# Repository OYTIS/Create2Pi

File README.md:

# Pi HAT for iRobot Create

iRobot Create Open Interface is a 7-pin mini-DIN connector exposing unregulated battery power pin and 5V UART. The HAT contains a power regulator to convert the battery power to 5V, and a level shifter to interface Roomba UART with Raspberry's 3.3V UART. Also a USB-Serial interface is added for convenience.

## Quickstart
TODO (when software is done)

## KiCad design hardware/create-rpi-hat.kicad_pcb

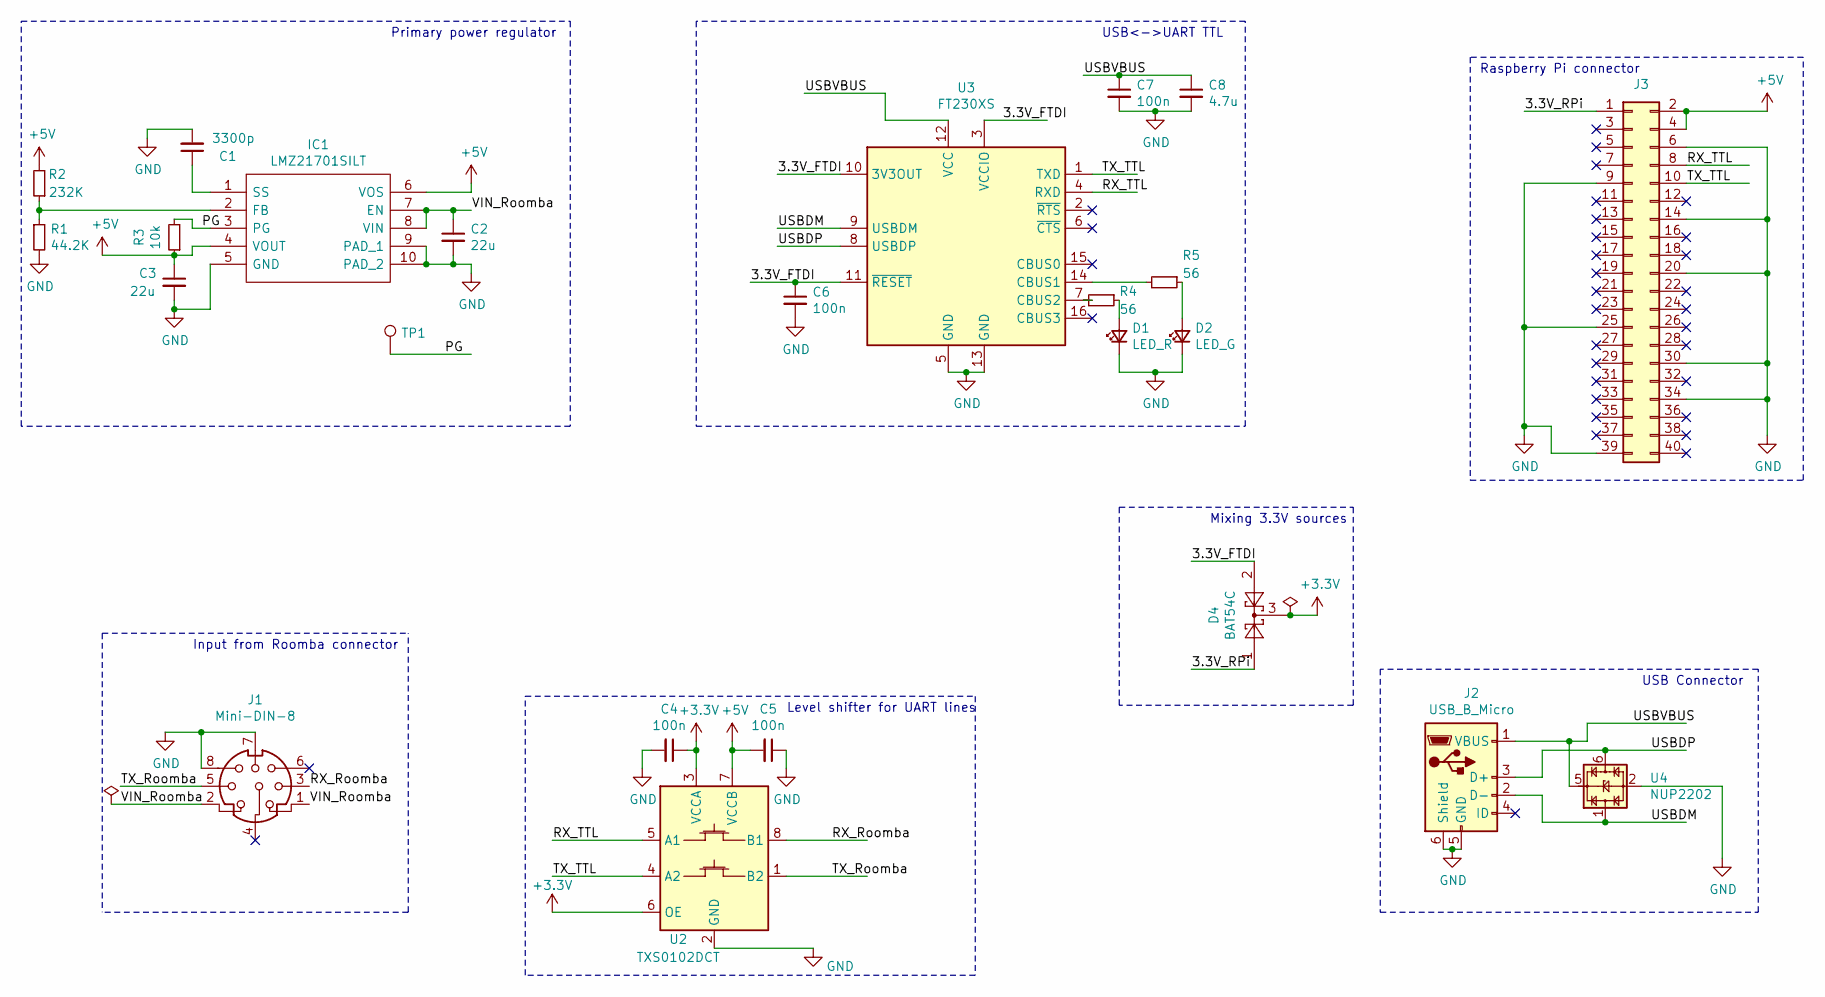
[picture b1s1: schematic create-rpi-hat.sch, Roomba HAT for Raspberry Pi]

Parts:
C1: 3300p; C_0402_1005Metric
C2, C3: 22u; C_0805_2012Metric_Pad1.15x1.40mm_HandSolder
C4, C5, C6, C7: 100n; C_0402_1005Metric
C8: 4.7u; C_0402_1005Metric
D1: LED_R; R_0402_1005Metric
D2: LED_G; R_0402_1005Metric
D4: BAT54C; SOT-23
IC1: LMZ21701SILT; SIL0008E; Mouser Part Number 595-LMZ21701SILT
J1: Mini-DIN-8; CUI_MD-80SM
J2: USB_B_Micro; USB_Micro-B_Molex-105017-0001
J3: RaspberryPi GPIO connector; PinSocket_2x20_P2.54mm_Vertical
R1: 44.2K; R_0402_1005Metric
R2: 232K; R_0402_1005Metric
R3: 10k; R_0402_1005Metric
R4, R5: 56; R_0402_1005Metric
TP1: TestPoint; TestPoint_Pad_D2.0mm
U2: TXS0102DCT; SSOP-8_2.95x2.8mm_P0.65mm
U3: FT230XS; SSOP-16_3.9x4.9mm_P0.635mm
U4: NUP2202; SOT-363_SC-70-6

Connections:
+3V3: C4.1, D4.3, U2.3 (VCCA), U2.6 (OE)
+5V: C3.1, C5.2, IC1.4 (VOUT), IC1.6 (VOS), J3.2, J3.4, R2.2, R3.1, U2.7 (VCCB)
/3.3V_FTDI: C6.1, D4.2, U3.3 (VCCIO), U3.10 (3V3OUT), U3.11 (~RESET)
/3.3V_RPi: D4.1, J3.1
/PG: IC1.3 (PG), R3.2, TP1.1
/RX_Roomba: J1.3, U2.8 (B1)
/RX_TTL: J3.8, U2.5 (A1), U3.4 (RXD)
/TX_Roomba: J1.5, U2.1 (B2)
/TX_TTL: J3.10, U2.4 (A2), U3.1 (TXD)
/USBDM: J2.2 (D-), U3.9 (USBDM), U4.1
/USBDP: J2.3 (D+), U3.8 (USBDP), U4.6
/USBVBUS: C7.1, C8.1, J2.1 (VBUS), U3.12 (VCC), U4.5
/VIN_Roomba: C2.1, IC1.7 (EN), IC1.8 (VIN), J1.1, J1.2
GND: C1.2, C2.2, C3.2, C4.2, C5.1, C6.2, C7.2, C8.2, D1.1 (K), D2.1 (K), IC1.5 (GND), IC1.9 (PAD_1), IC1.10 (PAD_2), J1.7, J1.8, J2.5 (GND), J2.6 (Shield), J3.6, J3.9, J3.14, J3.20, J3.25, J3.30, J3.34, J3.39, R1.2, U2.2 (GND), U3.5 (GND), U3.13 (GND), U4.2
unnamed: C1.1, IC1.1 (SS)
unnamed: D1.2 (A), R4.1
unnamed: D2.2 (A), R5.1
unnamed: IC1.2 (FB), R1.1, R2.1
unnamed: R4.2, U3.7 (CBUS2)
unnamed: R5.2, U3.14 (CBUS1)

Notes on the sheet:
Input from Roomba connector
Primary power regulator
Level shifter for UART lines
USB<->UART TTL
USB Connector
Raspberry Pi connector
Mixing 3.3V sources

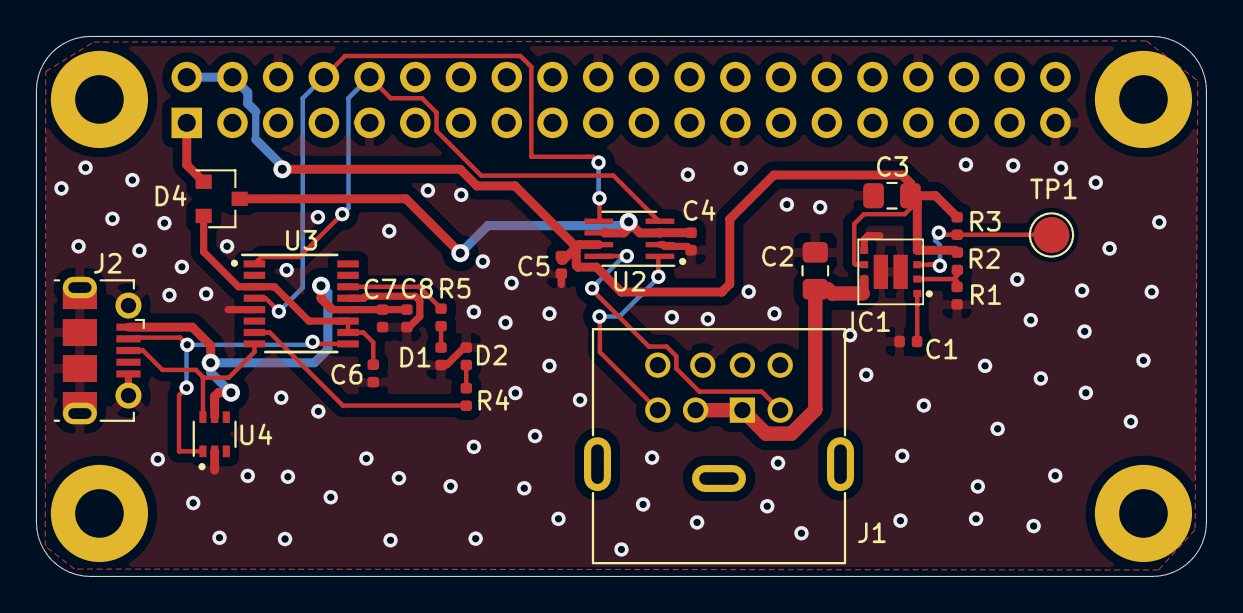
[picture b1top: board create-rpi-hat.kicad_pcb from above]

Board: 2 copper layers, 65.0 x 30.0 mm, 24 parts (1 on the bottom side), 20 nets.

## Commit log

2020-05-14 Initial commit (hopefully with a working hardware design)
2020-05-17 Removed power pours and made more space for the buck module
    The latter is against module's layout recommendations, but makes
    soldering/rework easier
2020-06-01 Add a bit of vanity
2020-06-01 Add Digikey BOM
2020-07-09 First revision (ordered on Aisler) and postmortem
2020-08-02 Revision 0.9 (also ordered on Aisler)
2020-08-02 Update outputs
